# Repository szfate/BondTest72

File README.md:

# BondTest72

Production test fixture board for bond wire testing, controlled by a Raspberry Pi Pico.
Test signals are routed through CH446X analog crosspoint switches to two 41-pin connectors, on which a replaceable adapter board sits. The adapter board carries the DUT connector and any auxiliary components, keeping the main tester board from wearing out.

## Specifications

| Parameter | Value |
|-----------|-------|
| Revision | r2 |
| Date | 2026-09-20 |
| Board size | 80 × 90 mm |
| Layers | 4 (F.Cu / In1.Cu / In2.Cu / B.Cu) |
| Thickness | 1.6 mm FR4 |

## Power

The board is powered from the Pico's USB VBUS rail. The TPS7A0533 LDO provides an optional quiet +3.3VADC rail as an alternative ADC reference, in case the main +3.3V rail from the Pico's onboard DCDC is too noisy. In practice the application only requires ~0.1 V accuracy, so the main rail is likely sufficient.

An ICL7660 charge-pump voltage inverter (or equivalent) generates the negative VEE rail required by the CH446X analog crosspoint switches.

## Operator Interface

A single push button serves as the START control. The two SK6812 RGB LEDs serve as status indicators. Both the LEDs and the button sit on the right edge of the board so the prodcution panel cannot cover them.

## Signal Routing

Four CH446X analog crosspoint switches fan test signals out from the Pico GPIO/ADC lines to the 41-pin connectors (J3 / J4). These connect to a removable **adapter board** rather than directly to the DUT. The adapter board carries the DUT-side connector (the high-wear part) and any auxiliary components needed for a given test configuration — for example, diodes for self-testing or a small memory chip for wear-cycle monitoring. Replacing the adapter board instead of the whole fixture avoids discarding the tester after the DUT connector wears out (~100 cycles). Solder jumpers on the main board provide flexibility to work around any schematic design flaws discovered after fabrication.

## Revision History

### r2 (2026-09-21)

Schematic:
- Neighbour testing removed, replaced with 10 µA / 100 µA / 1 mA current sources; pullup resistors (280 kΩ / 27.4 kΩ / 2.49 kΩ) sized from the expected diode voltage drop at each current
- ICL7660 (or alternative) added for the negative VEE supply
- 100 kΩ pulldown on Pico pad 22 (CON6, EEPROM SIO)
- 10 kΩ pullup on Pico pad 1 (START) per the RP2350 A2 errata
- 120 pF capacitor added to the ADC sensing net
- Status LEDs reduced from three to two SK6812
- Push button changed to EVP-BT3C4A000; r1's alternate second switch footprint removed

PCB:
- Board size reduced from 80 × 100 mm to 80 × 90 mm
- LEDs and button moved to the right side of the board so the panel no longer covers the LEDs; Space left for button caps
- Feet marks on the bottom silk enlarged from 8 mm to 10 mm

### r1 (2026-05-12)

Initial release. 80 × 100 mm.

## Files

| File | Description |
|------|-------------|
| `BondTest72.kicad_pro` | KiCad project |
| `BondTest72.kicad_sch` | Schematic |
| `BondTest72.kicad_pcb` | PCB layout |
| `docs/BondTest72-r2-schematic.pdf` | r2 schematic PDF export |
| `docs/BondTest72-r1-schematic.pdf` | r1 schematic PDF export |
| `production/BondTest72-r2.zip` | r2 gerber/fabrication outputs |
| `production/BondTest72-r2-bom.csv` | r2 bill of materials |
| `production/BondTest72-r2-pos.xlsx` | r2 pick-and-place positions |
| `lib.kicad_sym` | Project symbol library |
| `lib.pretty/` | Project footprint library |
| `df9.pretty/` | Additional footprint library |
| `docs/` | Board renders and documentation images |

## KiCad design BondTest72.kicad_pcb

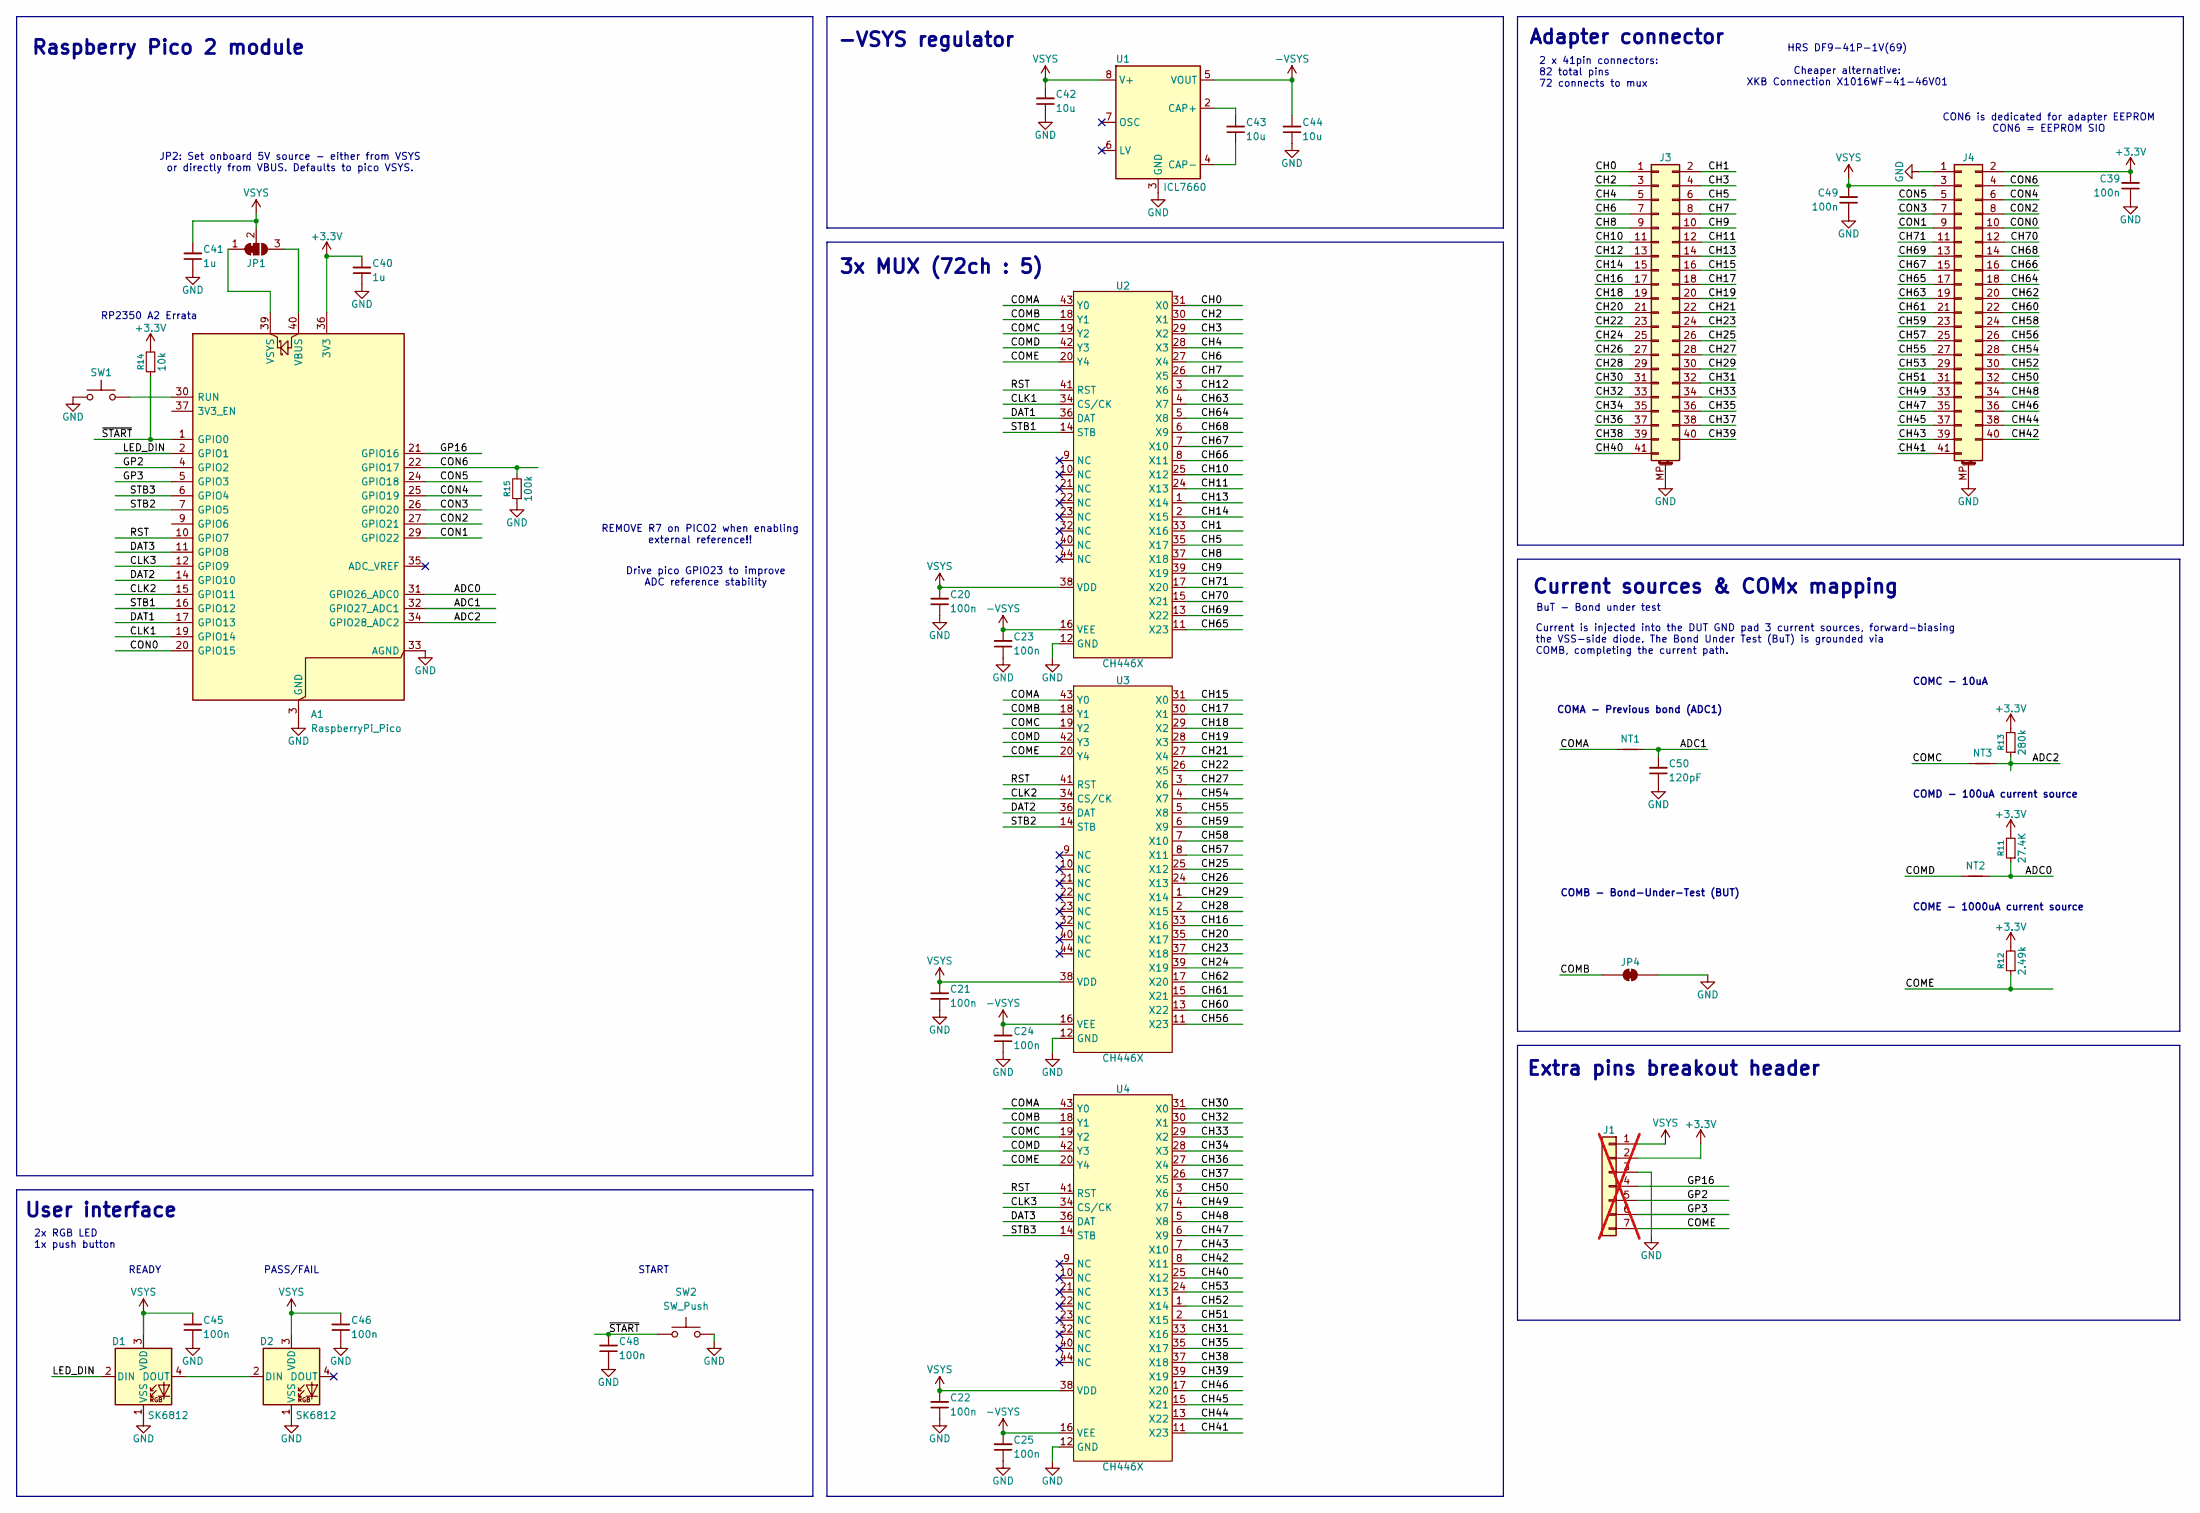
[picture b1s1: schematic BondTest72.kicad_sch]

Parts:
A1: RaspberryPi_Pico; RaspberryPi_Pico_Common_Unspecified; Part Number C41407547
C20, C21, C22, C23, C24, C25, C39, C45, C46, C48, C49: 100n; C_0201_0603Metric; Part Number C76939
C40, C41: 1u; C_0201_0603Metric; Part Number C170153
C42, C43, C44: 10u; C_1206_3216Metric; Part Number C9807
C50: 120pF; C_0201_0603Metric; Part Number C161405
D1, D2: SK6812; LED_SK6812_PLCC4_5.0x5.0mm_P3.2mm; Part Number C5378720
J1: Conn_01x07; PinHeader_1x07_P2.54mm_Vertical; not fitted
J3, J4: Conn_2Rows-41Pins_MountingPin; DF9-41P-1V; Part Number C21261706
JP1: SolderJumper_3_Bridged12; SolderJumper-3_P1.3mm_Bridged12_RoundedPad1.0x1.5mm_NumberL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
JP4: SolderJumper_2_Bridged; SolderJumper-2_P1.3mm_Bridged_RoundedPad1.0x1.5mm
NT1, NT2, NT3: NetTie_2; NetTie-2_SMD_Pad0.15mm
R11: 27.4K; R_0201_0603Metric; Part Number C273316
R12: 2.49k; R_0201_0603Metric; Part Number C851701
R13: 280k; R_0201_0603Metric; Part Number C778392
R14: 10k; R_0201_0603Metric; Part Number C106225
R15: 100k; R_0201_0603Metric; Part Number C106224
SW1: SW_Push; SW_SPST_EVQQ2; Part Number C713484
SW2: SW_Push; SW_SPST_EVPBF; Part Number C4365008
U1: ICL7660; SOIC-8_3.9x4.9mm_P1.27mm; Part Number C356724
U2, U3, U4: CH446X; LQFP-44_10x10mm_P0.8mm; Part Number C3018882

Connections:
+3.3V: A1.36 (3V3), C39.2, C40.2, J1.2, J4.2, R11.2, R12.2, R13.2, R14.2
-VSYS: C23.2, C24.2, C25.2, C44.2, U1.5 (VOUT), U2.16 (VEE), U3.16 (VEE), U4.16 (VEE)
/ADC0: A1.31 (GPIO26_ADC0), NT2.2, R11.1
/ADC1: A1.32 (GPIO27_ADC1), C50.2, NT1.2
/ADC2: A1.34 (GPIO28_ADC2), NT3.2, R13.1
/CH0: J3.1, U2.31 (X0)
/CH1: J3.2, U2.33 (X16)
/CH2: J3.3, U2.30 (X1)
/CH3: J3.4, U2.29 (X2)
/CH4: J3.5, U2.28 (X3)
/CH5: J3.6, U2.35 (X17)
/CH6: J3.7, U2.27 (X4)
/CH7: J3.8, U2.26 (X5)
/CH8: J3.9, U2.37 (X18)
/CH9: J3.10, U2.39 (X19)
/CH10: J3.11, U2.25 (X12)
/CH11: J3.12, U2.24 (X13)
/CH12: J3.13, U2.3 (X6)
/CH13: J3.14, U2.1 (X14)
/CH14: J3.15, U2.2 (X15)
/CH15: J3.16, U3.31 (X0)
/CH16: J3.17, U3.33 (X16)
/CH17: J3.18, U3.30 (X1)
/CH18: J3.19, U3.29 (X2)
/CH19: J3.20, U3.28 (X3)
/CH20: J3.21, U3.35 (X17)
/CH21: J3.22, U3.27 (X4)
/CH22: J3.23, U3.26 (X5)
/CH23: J3.24, U3.37 (X18)
/CH24: J3.25, U3.39 (X19)
/CH25: J3.26, U3.25 (X12)
/CH26: J3.27, U3.24 (X13)
/CH27: J3.28, U3.3 (X6)
/CH28: J3.29, U3.2 (X15)
/CH29: J3.30, U3.1 (X14)
/CH30: J3.31, U4.31 (X0)
/CH31: J3.32, U4.33 (X16)
/CH32: J3.33, U4.30 (X1)
/CH33: J3.34, U4.29 (X2)
/CH34: J3.35, U4.28 (X3)
/CH35: J3.36, U4.35 (X17)
/CH36: J3.37, U4.27 (X4)
/CH37: J3.38, U4.26 (X5)
/CH38: J3.39, U4.37 (X18)
/CH39: J3.40, U4.39 (X19)
/CH40: J3.41, U4.25 (X12)
/CH41: J4.41, U4.11 (X23)
/CH42: J4.40, U4.8 (X11)
/CH43: J4.39, U4.7 (X10)
/CH44: J4.38, U4.13 (X22)
/CH45: J4.37, U4.15 (X21)
/CH46: J4.36, U4.17 (X20)
/CH47: J4.35, U4.6 (X9)
/CH48: J4.34, U4.5 (X8)
/CH49: J4.33, U4.4 (X7)
/CH50: J4.32, U4.3 (X6)
/CH51: J4.31, U4.2 (X15)
/CH52: J4.30, U4.1 (X14)
/CH53: J4.29, U4.24 (X13)
/CH54: J4.28, U3.4 (X7)
/CH55: J4.27, U3.5 (X8)
/CH56: J4.26, U3.11 (X23)
/CH57: J4.25, U3.8 (X11)
/CH58: J4.24, U3.7 (X10)
/CH59: J4.23, U3.6 (X9)
/CH60: J4.22, U3.13 (X22)
/CH61: J4.21, U3.15 (X21)
/CH62: J4.20, U3.17 (X20)
/CH63: J4.19, U2.4 (X7)
/CH64: J4.18, U2.5 (X8)
/CH65: J4.17, U2.11 (X23)
/CH66: J4.16, U2.8 (X11)
/CH67: J4.15, U2.7 (X10)
/CH68: J4.14, U2.6 (X9)
/CH69: J4.13, U2.13 (X22)
/CH70: J4.12, U2.15 (X21)
/CH71: J4.11, U2.17 (X20)
/CLK1: A1.19 (GPIO14), U2.34 (CS/CK)
/CLK2: A1.15 (GPIO11), U3.34 (CS/CK)
/CLK3: A1.12 (GPIO9), U4.34 (CS/CK)
/COMA: NT1.1, U2.43 (Y0), U3.43 (Y0), U4.43 (Y0)
/COMB: JP4.1 (A), U2.18 (Y1), U3.18 (Y1), U4.18 (Y1)
/COMC: NT3.1, U2.19 (Y2), U3.19 (Y2), U4.19 (Y2)
/COMD: NT2.1, U2.42 (Y3), U3.42 (Y3), U4.42 (Y3)
/COME: J1.7, R12.1, U2.20 (Y4), U3.20 (Y4), U4.20 (Y4)
/CON0: A1.20 (GPIO15), J4.10
/CON1: A1.29 (GPIO22), J4.9
/CON2: A1.27 (GPIO21), J4.8
/CON3: A1.26 (GPIO20), J4.7
/CON4: A1.25 (GPIO19), J4.6
/CON5: A1.24 (GPIO18), J4.5
/CON6: A1.22 (GPIO17), J4.4, R15.2
/DAT1: A1.17 (GPIO13), U2.36 (DAT)
/DAT2: A1.14 (GPIO10), U3.36 (DAT)
/DAT3: A1.11 (GPIO8), U4.36 (DAT)
/GP2: A1.4 (GPIO2), J1.5
/GP3: A1.5 (GPIO3), J1.6
/GP16: A1.21 (GPIO16), J1.4
/LED_DIN: A1.2 (GPIO1), D1.2 (DIN)
/RST: A1.10 (GPIO7), U2.41 (RST), U3.41 (RST), U4.41 (RST)
/STB1: A1.16 (GPIO12), U2.14 (STB)
/STB2: A1.7 (GPIO5), U3.14 (STB)
/STB3: A1.6 (GPIO4), U4.14 (STB)
/~START: A1.1 (GPIO0), C48.2, R14.1, SW2.1
GND: A1.3 (GND), A1.8 (GND), A1.13 (GND), A1.18 (GND), A1.23 (GND), A1.28 (GND), A1.33 (AGND), A1.38 (GND), C20.1, C21.1, C22.1, C23.1, C24.1, C25.1, C39.1, C40.1, C41.1, C42.1, C44.1, C45.1, C46.1, C48.1, C49.1, C50.1, D1.1 (VSS), D2.1 (VSS), J1.3, J3.MP (MountPin), J4.1, J4.MP (MountPin), JP4.2 (B), R15.1, SW1.1, SW2.2, U1.3 (GND), U2.12 (GND), U3.12 (GND), U4.12 (GND)
unnamed: A1.30 (RUN), SW1.2
unnamed: A1.40 (VBUS), JP1.3 (B)
unnamed: A1.39 (VSYS), JP1.1 (A)
unnamed: D1.4 (DOUT), D2.2 (DIN)
unnamed: C43.2, U1.2 (CAP+)
unnamed: C43.1, U1.4 (CAP-)
VSYS: C20.2, C21.2, C22.2, C41.2, C42.2, C45.2, C46.2, C49.2, D1.3 (VDD), D2.3 (VDD), J1.1, J4.3, JP1.2 (C), U1.8 (V+), U2.38 (VDD), U3.38 (VDD), U4.38 (VDD)

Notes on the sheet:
3x MUX (72ch : 5)
Adapter connector
HRS DF9-41P-1V(69) Cheaper alternative: XKB Connection X1016WF-41-46V01
COMB - Bond-Under-Test (BUT)
READY
Raspberry Pico 2 module
Drive pico GPIO23 to improve ADC reference stability
COMD - 100uA current source
CON6 is dedicated for adapter EEPROM CON6 = EEPROM SIO
2x RGB LED 1x push button
REMOVE R7 on PICO2 when enabling external reference!!
Current sources & COMx mapping
COMC - 10uA
User interface
BuT - Bond under test
COME - 1000uA current source
-VSYS regulator
RP2350 A2 Errata
JP2: Set onboard 5V source - either from VSYS or directly from VBUS. Defaults to pico VSYS.
START
PASS/FAIL
2 x 41pin connectors: 82 total pins 72 connects to mux
Extra pins breakout header
COMA - Previous bond (ADC1)
Current is injected into the DUT GND pad 3 current sources, forward-biasing the VSS-side diode. The Bond Under Test (BuT) is grounded via COMB, completing the current path.

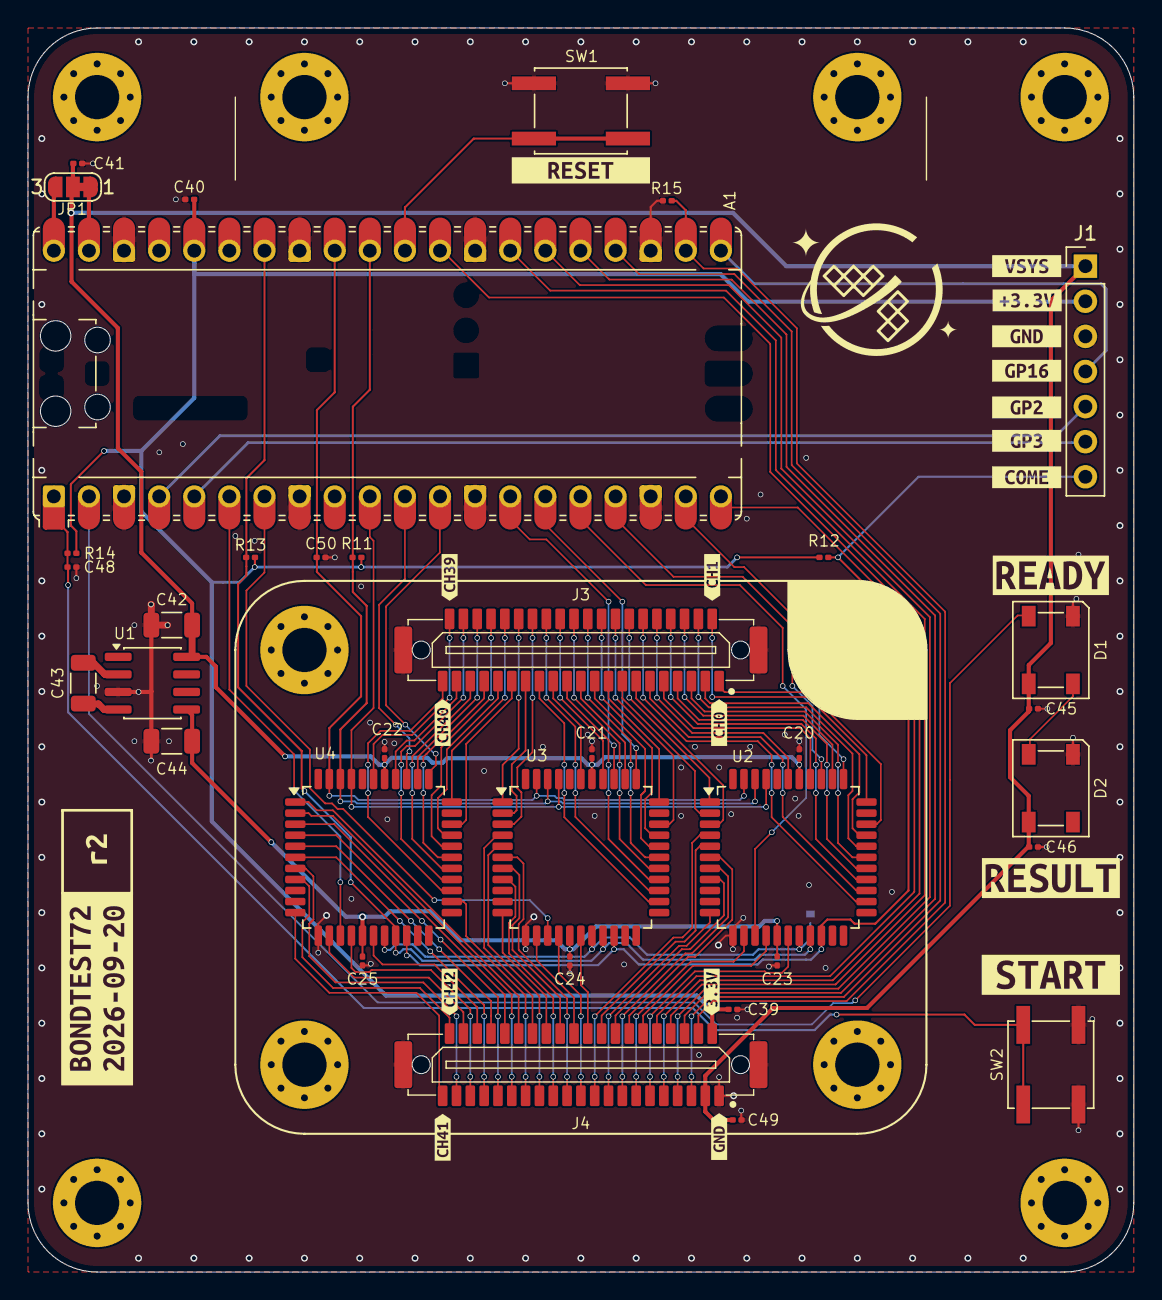
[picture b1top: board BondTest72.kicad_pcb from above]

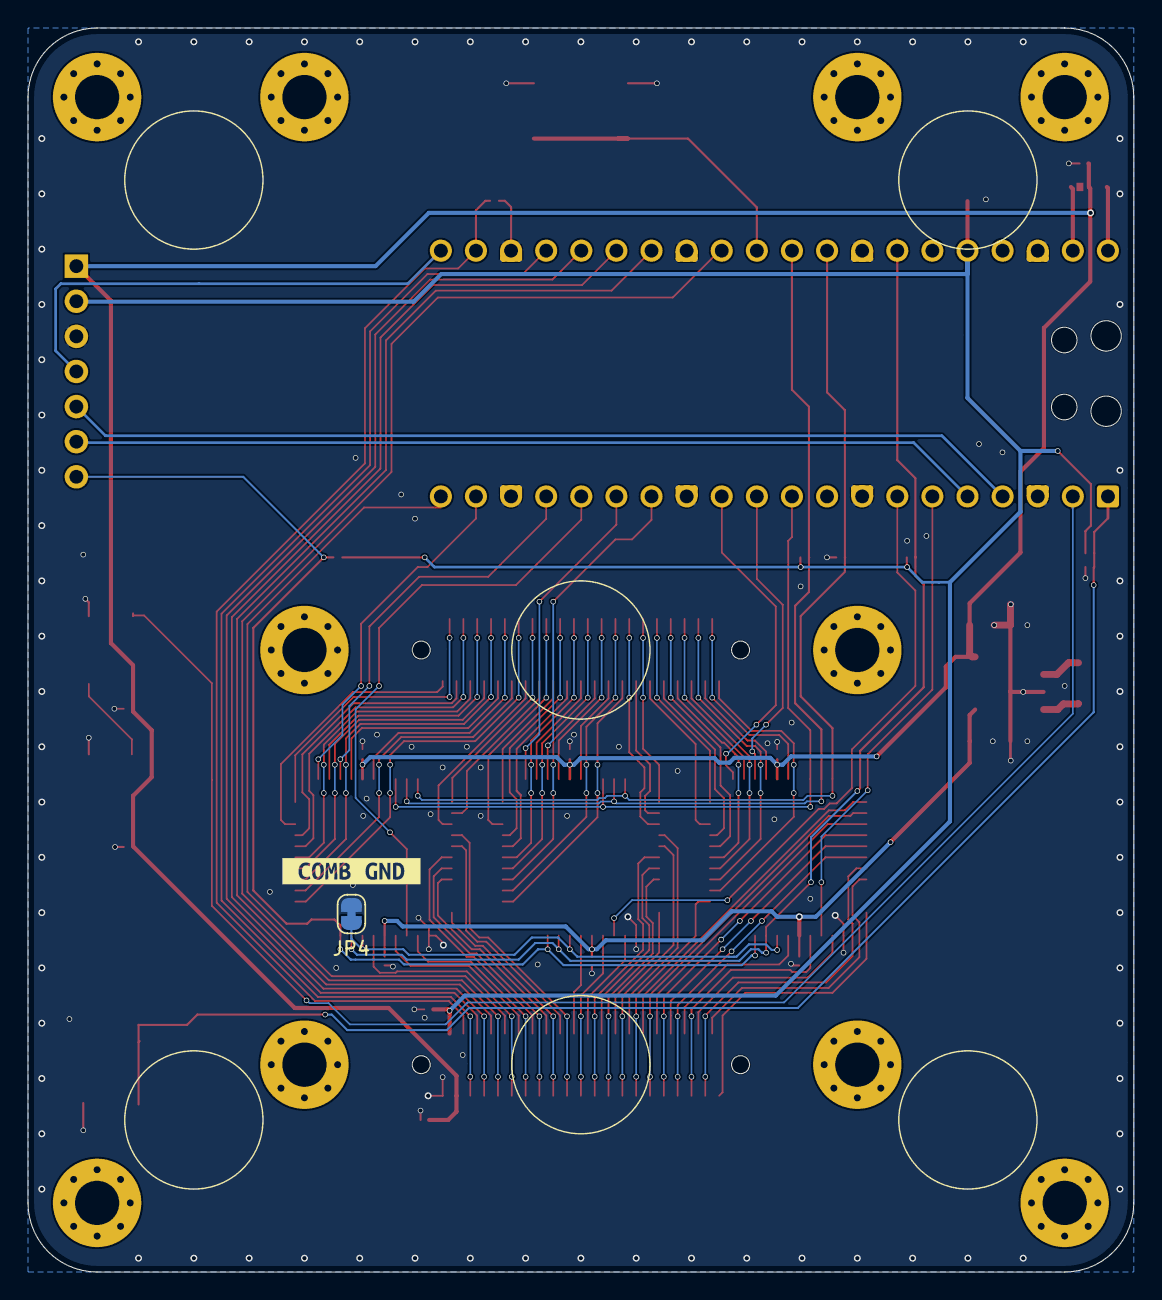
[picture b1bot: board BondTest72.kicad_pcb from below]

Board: 4 copper layers, 80.0 x 90.0 mm, 61 parts (2 on the bottom side), 112 nets.

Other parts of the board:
kibuzzard-6A01F8AF: G***; kibuzzard-6A01F8AF
kibuzzard-6A01F8BD: G***; kibuzzard-6A01F8BD
kibuzzard-6A01F62B: G***; kibuzzard-6A01F62B
kibuzzard-6A01F65D: G***; kibuzzard-6A01F65D
kibuzzard-6A01F81D: G***; kibuzzard-6A01F81D
kibuzzard-6A01F87F: G***; kibuzzard-6A01F87F
kibuzzard-6A01F88E: G***; kibuzzard-6A01F88E
kibuzzard-6A01F618: G***; kibuzzard-6A01F618
kibuzzard-6A01F644: G***; kibuzzard-6A01F644
kibuzzard-6A01F655: G***; kibuzzard-6A01F655
kibuzzard-6A01F806: G***; kibuzzard-6A01F806
kibuzzard-6A01FB9A: G***; kibuzzard-6A01FB9A
kibuzzard-6A01FE13: G***; kibuzzard-6A01FE13
kibuzzard-6A02A7B4: G***; kibuzzard-6A02A7B4
kibuzzard-6A02FF2D: G***; kibuzzard-6A02FF2D
kibuzzard-6A02760F: G***; kibuzzard-6A02760F
kibuzzard-6A027603: G***; kibuzzard-6A027603
kibuzzard-6A030225: G***; kibuzzard-6A030225
kibuzzard-6AAFDF39: G***; kibuzzard-6AAFDF39
kibuzzard-6AAFDFCA: G***; kibuzzard-6AAFDFCA
kibuzzard-6AAFFF2E: G***; kibuzzard-6AAFFF2E
kibuzzard-6AAFFF26: G***; kibuzzard-6AAFFF26

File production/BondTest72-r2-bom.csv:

Reference,Qty,Value,DNP,Exclude from BOM,Exclude from Board,Footprint,Datasheet,Part Number
A1,1,RaspberryPi_Pico,,,,Module:RaspberryPi_Pico_Common_Unspecified,https://datasheets.raspberrypi.com/pico/pico-datasheet.pdf,C41407547
"C20,C21,C22,C23,C24,C25,C39,C45,C46,C48,C49",11,100n,,,,Capacitor_SMD:C_0201_0603Metric,,C76939
"C40,C41",2,1u,,,,Capacitor_SMD:C_0201_0603Metric,,C170153
"C42,C43,C44",3,10u,,,,Capacitor_SMD:C_1206_3216Metric,,C9807
C50,1,120pF,,,,Capacitor_SMD:C_0201_0603Metric,,C161405
"D1,D2",2,SK6812,,,,LED_SMD:LED_SK6812_PLCC4_5.0x5.0mm_P3.2mm,https://cdn-shop.adafruit.com/product-files/1138/SK6812+LED+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,C5378720
J1,1,Conn_01x07,DNP,,,Connector_PinHeader_2.54mm:PinHeader_1x07_P2.54mm_Vertical,,
"J3,J4",2,Conn_2Rows-41Pins_MountingPin,,,,df9:DF9-41P-1V,,C21261706
R11,1,27.4K,,,,Resistor_SMD:R_0201_0603Metric,,C273316
R12,1,2.49k,,,,Resistor_SMD:R_0201_0603Metric,,C851701
R13,1,280k,,,,Resistor_SMD:R_0201_0603Metric,,C778392
R14,1,10k,,,,Resistor_SMD:R_0201_0603Metric,,C106225
R15,1,100k,,,,Resistor_SMD:R_0201_0603Metric,,C106224
SW1,1,SW_Push,,,,Button_Switch_SMD:SW_SPST_EVQQ2,,C713484
SW2,1,SW_Push,,,,Button_Switch_SMD:SW_SPST_EVPBF,,C4365008
U1,1,ICL7660,,,,Package_SO:SOIC-8_3.9x4.9mm_P1.27mm,http://datasheets.maximintegrated.com/en/ds/ICL7660-MAX1044.pdf,C356724
"U2,U3,U4",3,CH446X,,,,Package_QFP:LQFP-44_10x10mm_P0.8mm,,C3018882

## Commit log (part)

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2026-05-17 Initial commit. Adding already fabricated r1 files.
2026-05-18 Add a new R2 TODO.
